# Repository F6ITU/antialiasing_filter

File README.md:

Cerberus, a triple path antialiasing filter for RF Software defined radio

Cerberus is a simple series of three 52 MHz low pass filters designed to eliminate the second Nyquist zone of any "bare foot" 
120 MSPS baseband software defined HF transceiver. One filter is used in the Transmission path, two distinct filters could be used for 
two different RX path.

A single LTCC filter is dedicated to the TX output able to withstand up to 8W CW. It's rejection level is around 50 dB in the stopband area.
This filter should be  completed with a post-amplifier low pass filter. 

Two RX path (for 2 separated ADCs) are based on a pair of cascaded RLP-50+ low pass filters, thus offering a rejection of 50 dB each

Each of these path could be used with or without an RF preselector (bandpass filter or low pass filter) 

This antialiasing frontend should be inserted just after the baseband board (Red Pitaya 14 or 16 bits, IQsdr etc)and before 
the SDR frontend (in other words, a simple bandpass filter, a more complex "Alexiares like" preselector, or a combination of 
Alexiares or entry level filters and a set of high power frontend (Zolotaref lpf, Aries ATU, Munin amplifier etc

As usual, this board is under the CERN Open Hardware licence

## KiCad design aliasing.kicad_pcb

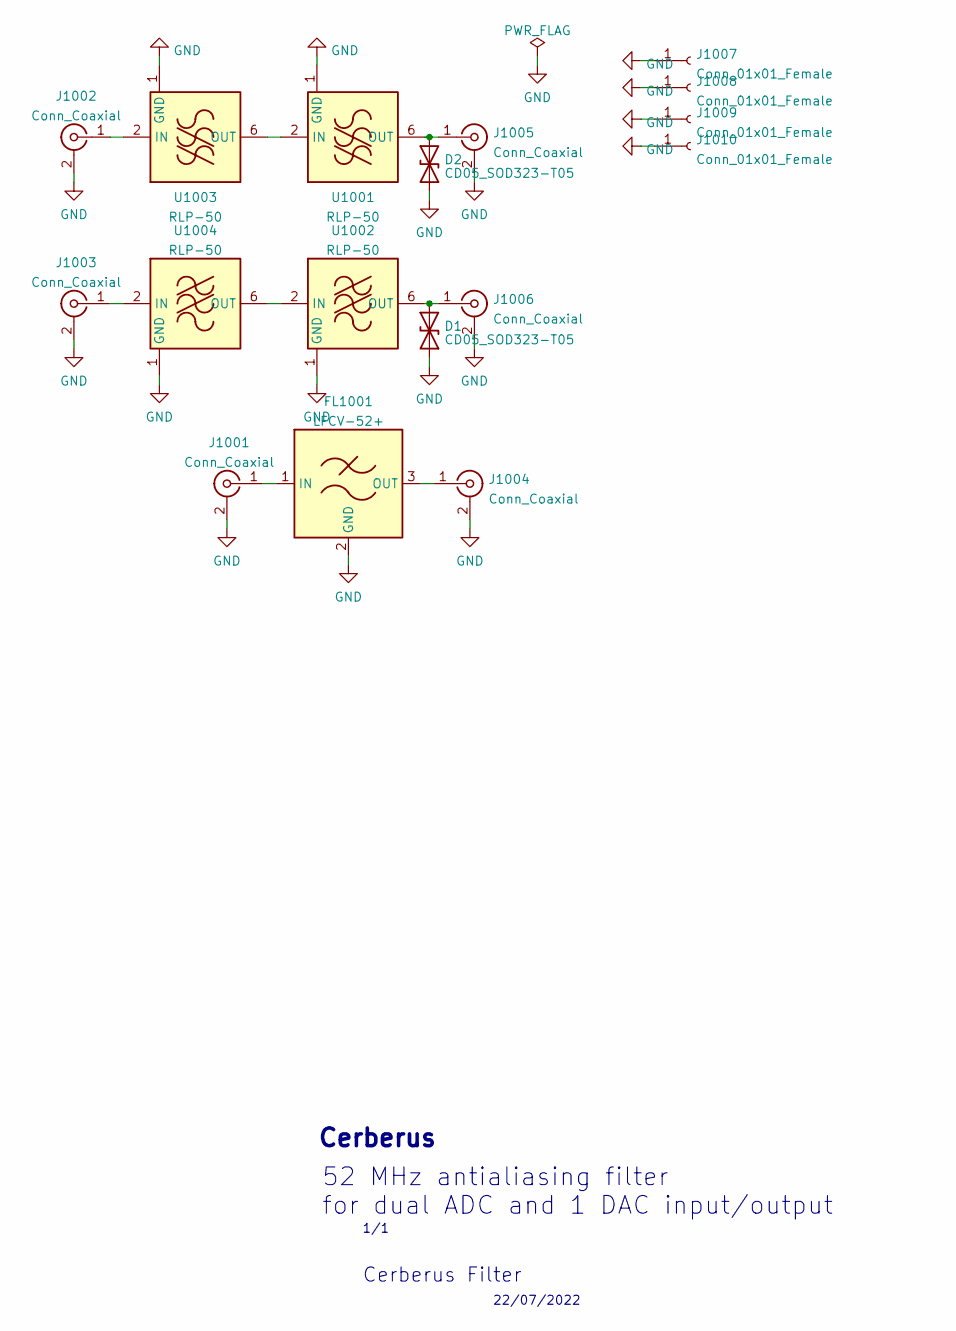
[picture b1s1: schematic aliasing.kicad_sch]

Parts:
D1, D2: CD05_SOD323-T05; D_SOD-323
FL1001: LFCV-52+; Filter_Mini-Circuits_FV1206
J1001, J1002, J1003, J1004, J1005, J1006: Conn_Coaxial; SMA_PINS
J1007, J1008, J1009, J1010: Conn_01x01_Female; MountingHole_3.2mm_M3_ISO7380_Pad
U1001, U1002, U1003, U1004: RLP-50; Mini-Circuits_GP1212_LandPatternPL-176

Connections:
GND: D1.1 (A1), D2.1 (A1), FL1001.2 (GND), FL1001.4 (GND), J1001.2 (Ext), J1002.2 (Ext), J1003.2 (Ext), J1004.2 (Ext), J1005.2 (Ext), J1006.2 (Ext), J1007.1, J1008.1, J1009.1, J1010.1, U1001.1 (GND), U1001.3 (GND), U1001.4 (GND), U1001.5 (GND), U1001.7 (GND), U1001.8 (GND), U1002.1 (GND), U1002.3 (GND), U1002.4 (GND), U1002.5 (GND), U1002.7 (GND), U1002.8 (GND), U1003.1 (GND), U1003.3 (GND), U1003.4 (GND), U1003.5 (GND), U1003.7 (GND), U1003.8 (GND), U1004.1 (GND), U1004.3 (GND), U1004.4 (GND), U1004.5 (GND), U1004.7 (GND), U1004.8 (GND)
unnamed: D1.2 (A2), J1006.1 (In), U1002.6 (OUT)
unnamed: D2.2 (A2), J1005.1 (In), U1001.6 (OUT)
unnamed: FL1001.1 (IN), J1001.1 (In)
unnamed: FL1001.3 (OUT), J1004.1 (In)
unnamed: J1002.1 (In), U1003.2 (IN)
unnamed: J1003.1 (In), U1004.2 (IN)
unnamed: U1001.2 (IN), U1003.6 (OUT)
unnamed: U1002.2 (IN), U1004.6 (OUT)

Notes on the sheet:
22/07/2022
Cerberus
Cerberus Filter
52 MHz antialiasing filter for dual ADC and 1 DAC input/output
1/1

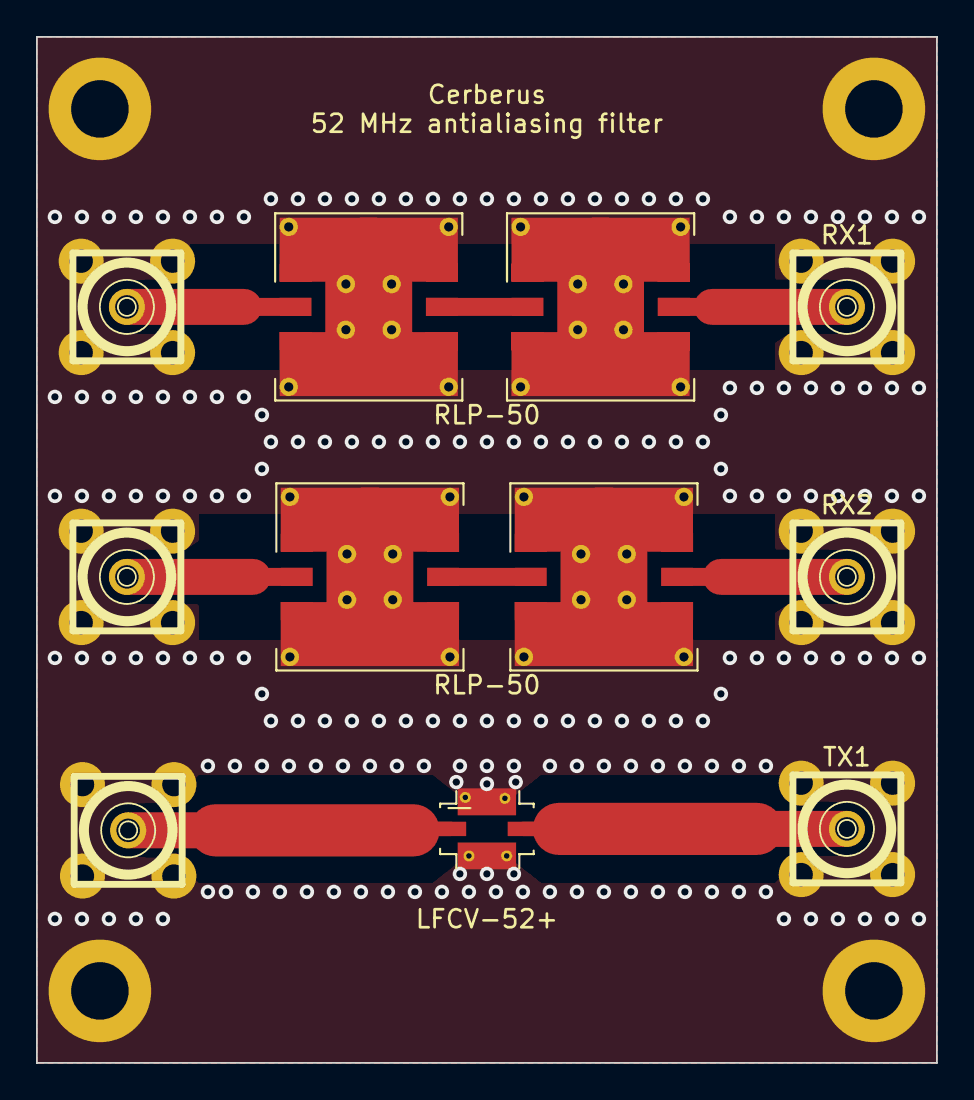
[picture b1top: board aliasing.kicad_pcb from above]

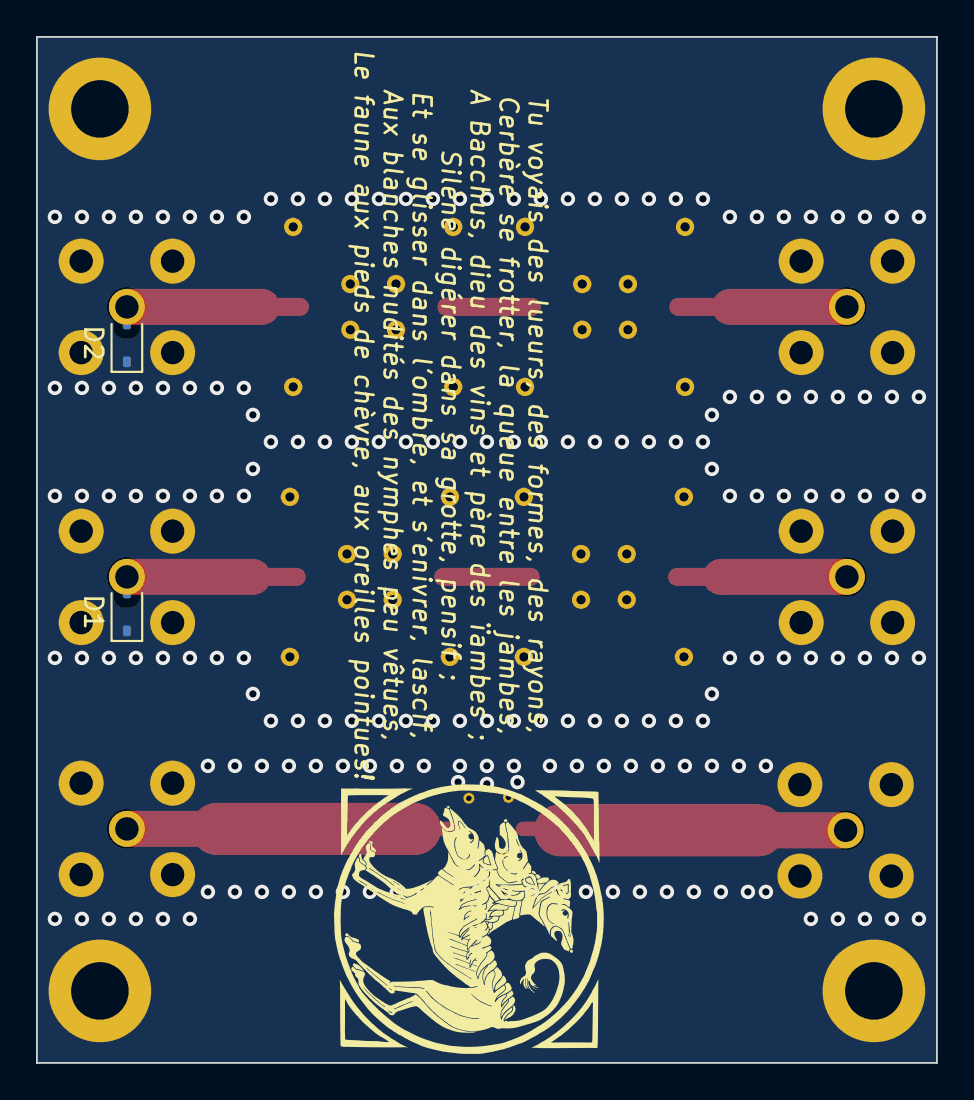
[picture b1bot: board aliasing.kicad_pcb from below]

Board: 2 copper layers, 50.0 x 57.0 mm, 17 parts (2 on the bottom side), 9 nets.

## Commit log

2022-07-22 first commit, pcb clean
2022-07-22 Silkmask cleaning, new set of Gerber files
2022-07-23 excentred mounting hole corrected
2022-07-23 excentred mounting hole corrected, new gerber
2022-08-08 new ibom, new picture, new readme
2022-08-15 minor changes in pcb and Readme
2023-04-16 TLV diodes added, new gerber, minor modif.
